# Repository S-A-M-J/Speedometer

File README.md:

# Speedometer
Speedometer based on 7 segment displays and esp32.
Kicad board file is for a Jeep Wrangler YJ.

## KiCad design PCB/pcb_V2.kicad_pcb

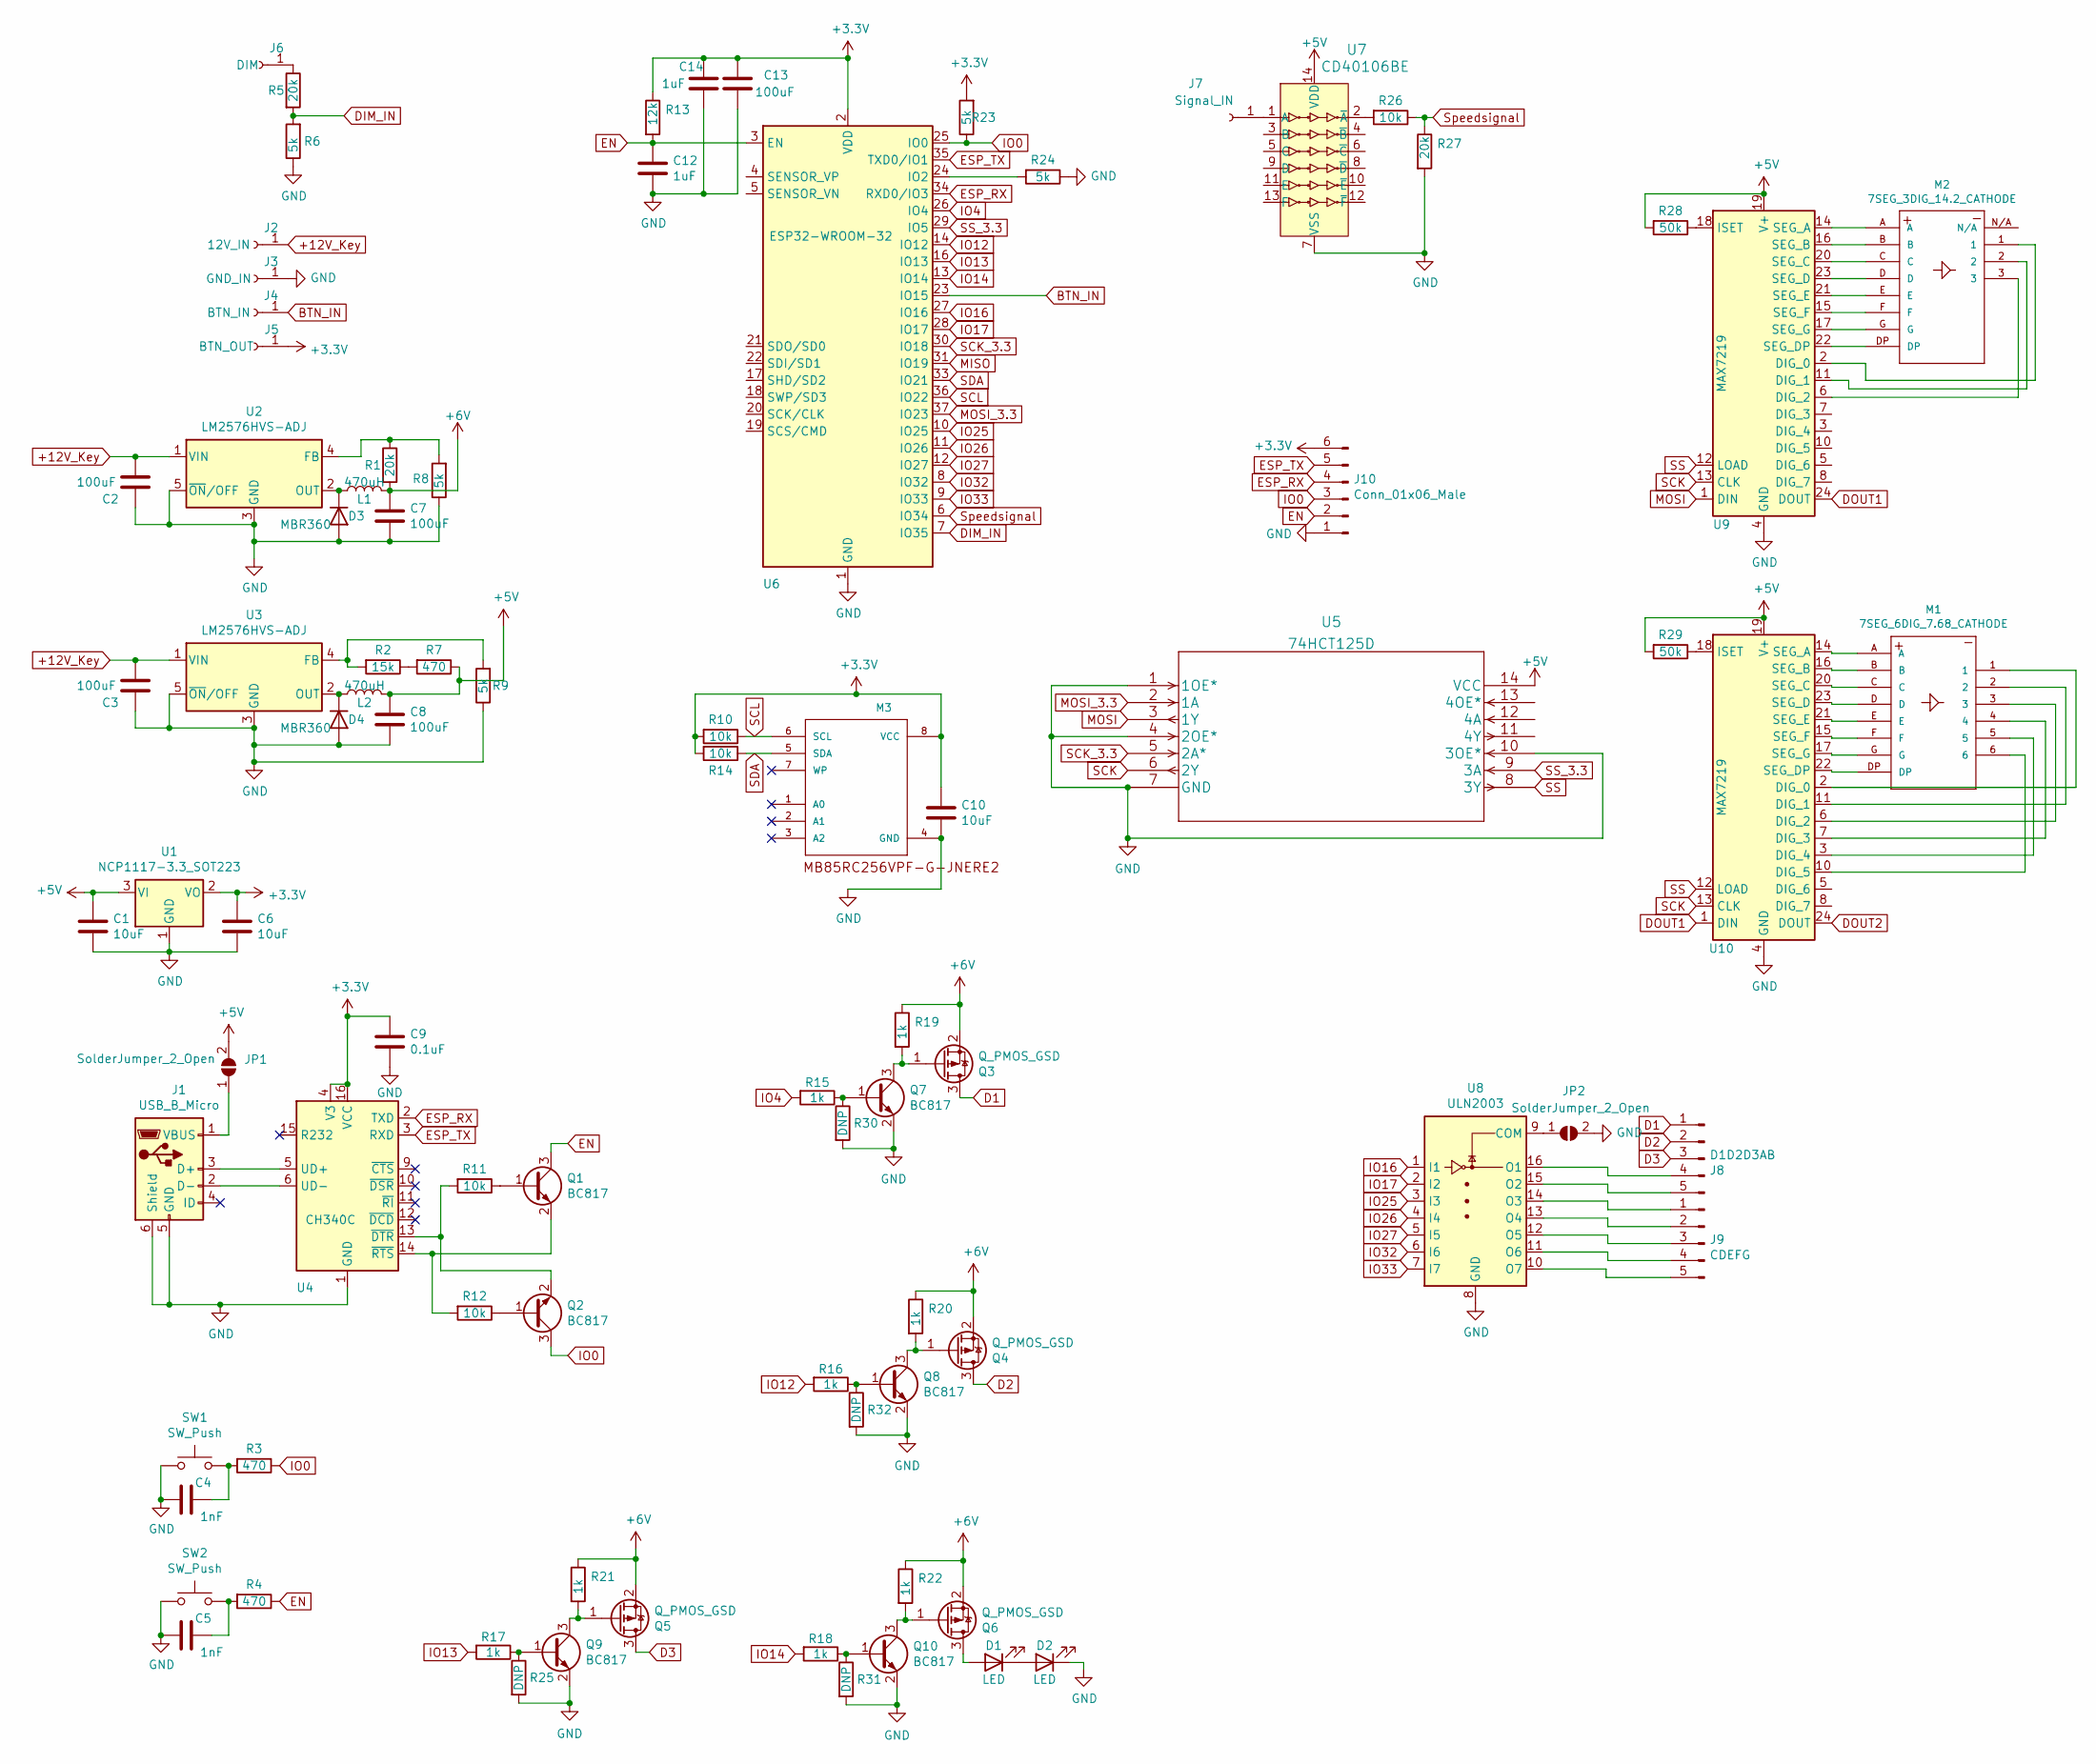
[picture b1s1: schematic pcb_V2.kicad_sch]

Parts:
C1, C6, C10: 10uF; C_0805_2012Metric_Pad1.18x1.45mm_HandSolder
C2, C3, C7, C8, C13: 100uF; CP_Elec_6.3x5.9
C4, C5: 1nF; C_0805_2012Metric_Pad1.18x1.45mm_HandSolder
C9: 0.1uF; C_0805_2012Metric_Pad1.18x1.45mm_HandSolder
C12, C14: 1uF; C_0805_2012Metric_Pad1.18x1.45mm_HandSolder
D1, D2: LED; D_0603_1608Metric_Pad1.05x0.95mm_HandSolder
D3, D4: MBR360; D_SMA_Handsoldering
J1: USB_B_Micro; USB_Micro-B_Molex-105017-0001
J2: 12V_IN; SolderWire-1.5sqmm_1x01_D1.7mm_OD3.9mm
J3: GND_IN; SolderWire-1.5sqmm_1x01_D1.7mm_OD3.9mm
J4: BTN_IN; SolderWire-1.5sqmm_1x01_D1.7mm_OD3.9mm
J5: BTN_OUT; SolderWire-1.5sqmm_1x01_D1.7mm_OD3.9mm
J6: DIM; SolderWire-1.5sqmm_1x01_D1.7mm_OD3.9mm
J7: Signal_IN; SolderWire-1.5sqmm_1x01_D1.7mm_OD3.9mm
J8: D1D2D3AB; PinHeader_1x05_P2.54mm_Vertical
J9: CDEFG; PinHeader_1x05_P2.54mm_Vertical
J10: Conn_01x06_Male; PinHeader_1x06_P2.54mm_Vertical
JP1, JP2: SolderJumper_2_Open; SolderJumper-2_P1.3mm_Open_Pad1.0x1.5mm
L1, L2: 470uH; L_12x12mm_H8mm
M1: 7SEG_6DIG_7.68_CATHODE; 7SEG_6DIG_7.68_Cathode
M2: 7SEG_3DIG_14.2_CATHODE; 7SEG_3DIG_14.2_Cathode
M3: MB85RC256VPF-G-JNERE2; SOP-8_5.28x5.23mm_P1.27mm
Q1, Q2, Q7, Q8, Q9, Q10: BC817; SOT-23
Q3, Q4, Q5, Q6: Q_PMOS_GSD; SOT-23
R1, R5, R27: 20k; R_0805_2012Metric_Pad1.20x1.40mm_HandSolder
R2: 15k; R_0805_2012Metric_Pad1.20x1.40mm_HandSolder
R3, R4, R7: 470; R_0805_2012Metric_Pad1.20x1.40mm_HandSolder
R6, R8, R9, R23, R24: 5k; R_0805_2012Metric_Pad1.20x1.40mm_HandSolder
R10, R11, R12, R14, R26: 10k; R_0805_2012Metric_Pad1.20x1.40mm_HandSolder
R13: 12k; R_0805_2012Metric_Pad1.20x1.40mm_HandSolder
R15, R16, R17, R18, R19, R20, R21, R22: 1k; R_0805_2012Metric_Pad1.20x1.40mm_HandSolder
R25, R30, R31, R32: DNP; R_0805_2012Metric_Pad1.20x1.40mm_HandSolder
R28, R29: 50k; R_0805_2012Metric_Pad1.20x1.40mm_HandSolder
SW1, SW2: SW_Push; SW_Push_1P1T_NO_6x6mm_H9.5mm
U1: NCP1117-3.3_SOT223; SOT-223-3_TabPin2
U2, U3: LM2576HVS-ADJ; TO-263-5_TabPin3
U4: CH340C; SOIC-16_3.9x9.9mm_P1.27mm
U5: 74HCT125D
U6: ESP32-WROOM-32
U7: CD40106BE; DIP-14_W7.62mm_LongPads; MPN CD40106BE; Digi-Key_PN 296-3503-5-ND
U8: ULN2003; SOP-16_4.55x10.3mm_P1.27mm
U9, U10: MAX7219; SOP-24_7.5x15.4mm_P1.27mm

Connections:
+3V3: C6.1, C9.2, C10.1, C13.1, C14.1, J5.1, J10.6, M3.8 (VCC), R10.2, R13.1, R14.2, R23.2, U1.2 (VO), U4.4 (V3), U4.16 (VCC), U6.2 (VDD)
+5V: C1.1, C8.1, JP1.2 (B), L2.2, R7.1, R28.2, R29.2, U1.3 (VI), U5.14 (VCC), U7.14 (VDD), U9.19 (V+), U10.19 (V+)
+6V: C7.1, L1.2, Q3.2 (S), Q4.2 (S), Q5.2 (S), Q6.2 (S), R1.2, R19.1, R20.1, R21.1, R22.1
+12V_Key: C2.1, C3.1, J2.1, U2.1 (VIN), U3.1 (VIN)
BTN_IN: J4.1, U6.23 (IO15)
D1: J8.1, Q3.3 (D)
D2: J8.2, Q4.3 (D)
D3: J8.3, Q5.3 (D)
DIM_IN: R5.2, R6.2, U6.7 (IO35)
DOUT1: U9.24 (DOUT), U10.1 (DIN)
DOUT2: U10.24 (DOUT)
EN: C12.1, J10.2, Q1.3 (C), R4.1, R13.2, U6.3 (EN)
ESP_RX: J10.4, U4.2 (TXD), U6.34 (RXD0/IO3)
ESP_TX: J10.5, U4.3 (RXD), U6.35 (TXD0/IO1)
GND: C1.2, C2.2, C3.2, C4.2, C5.2, C6.2, C7.2, C8.2, C9.1, C10.2, C12.2, C13.2, C14.2, D2.1 (K), D3.2 (A), D4.2 (A), J1.5 (GND), J1.6 (Shield), J3.1, J10.1, JP2.2 (B), M3.4 (GND), Q7.2 (E), Q8.2 (E), Q9.2 (E), Q10.2 (E), R6.1, R8.1, R9.1, R24.1, R25.2, R27.2, R30.2, R31.2, R32.2, SW1.1, SW2.1, U1.1 (GND), U2.3 (GND), U2.5 (~ON/OFF), U3.3 (GND), U3.5 (~ON/OFF), U4.1 (GND), U5.1 (1OE*), U5.4 (2OE*), U5.7 (GND), U5.10 (3OE*), U6.1 (GND), U6.15 (GND), U6.38 (GND), U6.39 (GND), U7.7 (VSS), U8.8 (GND), U9.4 (GND), U9.9 (GND), U10.4 (GND), U10.9 (GND)
IO0: J10.3, Q2.3 (C), R3.1, R23.1, U6.25 (IO0)
IO4: R15.2, U6.26 (IO4)
IO12: R16.2, U6.14 (IO12)
IO13: R17.2, U6.16 (IO13)
IO14: R18.2, U6.13 (IO14)
IO16: U6.27 (IO16), U8.1 (I1)
IO17: U6.28 (IO17), U8.2 (I2)
IO25: U6.10 (IO25), U8.3 (I3)
IO26: U6.11 (IO26), U8.4 (I4)
IO27: U6.12 (IO27), U8.5 (I5)
IO32: U6.8 (IO32), U8.6 (I6)
IO33: U6.9 (IO33), U8.7 (I7)
MISO: U6.31 (IO19)
MOSI: U5.3 (1Y), U9.1 (DIN)
MOSI_3.3: U5.2 (1A), U6.37 (IO23)
unnamed: C4.1, R3.2, SW1.2
unnamed: C5.1, R4.2, SW2.2
unnamed: D1.1 (K), D2.2 (A)
unnamed: D1.2 (A), Q6.3 (D)
unnamed: D3.1 (K), L1.1, U2.2 (OUT)
unnamed: D4.1 (K), L2.1, U3.2 (OUT)
unnamed: J1.1 (VBUS), JP1.1 (A)
unnamed: J1.2 (D-), U4.6 (UD-)
unnamed: J1.3 (D+), U4.5 (UD+)
unnamed: J6.1, R5.1
unnamed: J7.1, U7.1 (A)
unnamed: J8.4, U8.16 (O1)
unnamed: J8.5, U8.15 (O2)
unnamed: J9.1, U8.14 (O3)
unnamed: J9.2, U8.13 (O4)
unnamed: J9.3, U8.12 (O5)
unnamed: J9.4, U8.11 (O6)
unnamed: J9.5, U8.10 (O7)
unnamed: JP2.1 (A), U8.9 (COM)
unnamed: M1.1, U10.2 (DIG_0)
unnamed: M1.2, U10.11 (DIG_1)
unnamed: M1.3, U10.6 (DIG_2)
unnamed: M1.4, U10.7 (DIG_3)
unnamed: M1.5, U10.3 (DIG_4)
unnamed: M1.6, U10.10 (DIG_5)
unnamed: M1.A, U10.14 (SEG_A)
unnamed: M1.B, U10.16 (SEG_B)
unnamed: M1.C, U10.20 (SEG_C)
unnamed: M1.D, U10.23 (SEG_D)
unnamed: M1.DP, U10.22 (SEG_DP)
unnamed: M1.E, U10.21 (SEG_E)
unnamed: M1.F, U10.15 (SEG_F)
unnamed: M1.G, U10.17 (SEG_G)
unnamed: M2.1, U9.2 (DIG_0)
unnamed: M2.2, U9.11 (DIG_1)
unnamed: M2.3, U9.6 (DIG_2)
unnamed: M2.A, U9.14 (SEG_A)
unnamed: M2.B, U9.16 (SEG_B)
unnamed: M2.C, U9.20 (SEG_C)
unnamed: M2.D, U9.23 (SEG_D)
unnamed: M2.DP, U9.22 (SEG_DP)
unnamed: M2.E, U9.21 (SEG_E)
unnamed: M2.F, U9.15 (SEG_F)
unnamed: M2.G, U9.17 (SEG_G)
unnamed: Q1.1 (B), R11.1
unnamed: Q1.2 (E), R12.2, U4.14 (~RTS)
unnamed: Q2.1 (B), R12.1
unnamed: Q2.2 (E), R11.2, U4.13 (~DTR)
unnamed: Q3.1 (G), Q7.3 (C), R19.2
unnamed: Q4.1 (G), Q8.3 (C), R20.2
unnamed: Q5.1 (G), Q9.3 (C), R21.2
unnamed: Q7.1 (B), R15.1, R30.1
unnamed: Q8.1 (B), R16.1, R32.1
unnamed: Q9.1 (B), R17.1, R25.1
unnamed: Q10.1 (B), R18.1, R31.1
unnamed: Q6.1 (G), Q10.3 (C), R22.2
unnamed: R1.1, R8.2, U2.4 (FB)
unnamed: R2.1, R7.2
unnamed: R2.2, R9.2, U3.4 (FB)
unnamed: R24.2, U6.24 (IO2)
unnamed: R26.2, U7.2 (~A)
unnamed: R28.1, U9.18 (ISET)
unnamed: R29.1, U10.18 (ISET)
SCK: U5.6 (2Y), U9.13 (CLK), U10.13 (CLK)
SCK_3.3: U5.5 (2A*), U6.30 (IO18)
SCL: M3.6 (SCL), R10.1, U6.36 (IO22)
SDA: M3.5 (SDA), R14.1, U6.33 (IO21)
SS: U5.8 (3Y), U9.12 (LOAD), U10.12 (LOAD)
SS_3.3: U5.9 (3A), U6.29 (IO5)
Speedsignal: R26.1, R27.1, U6.6 (IO34)

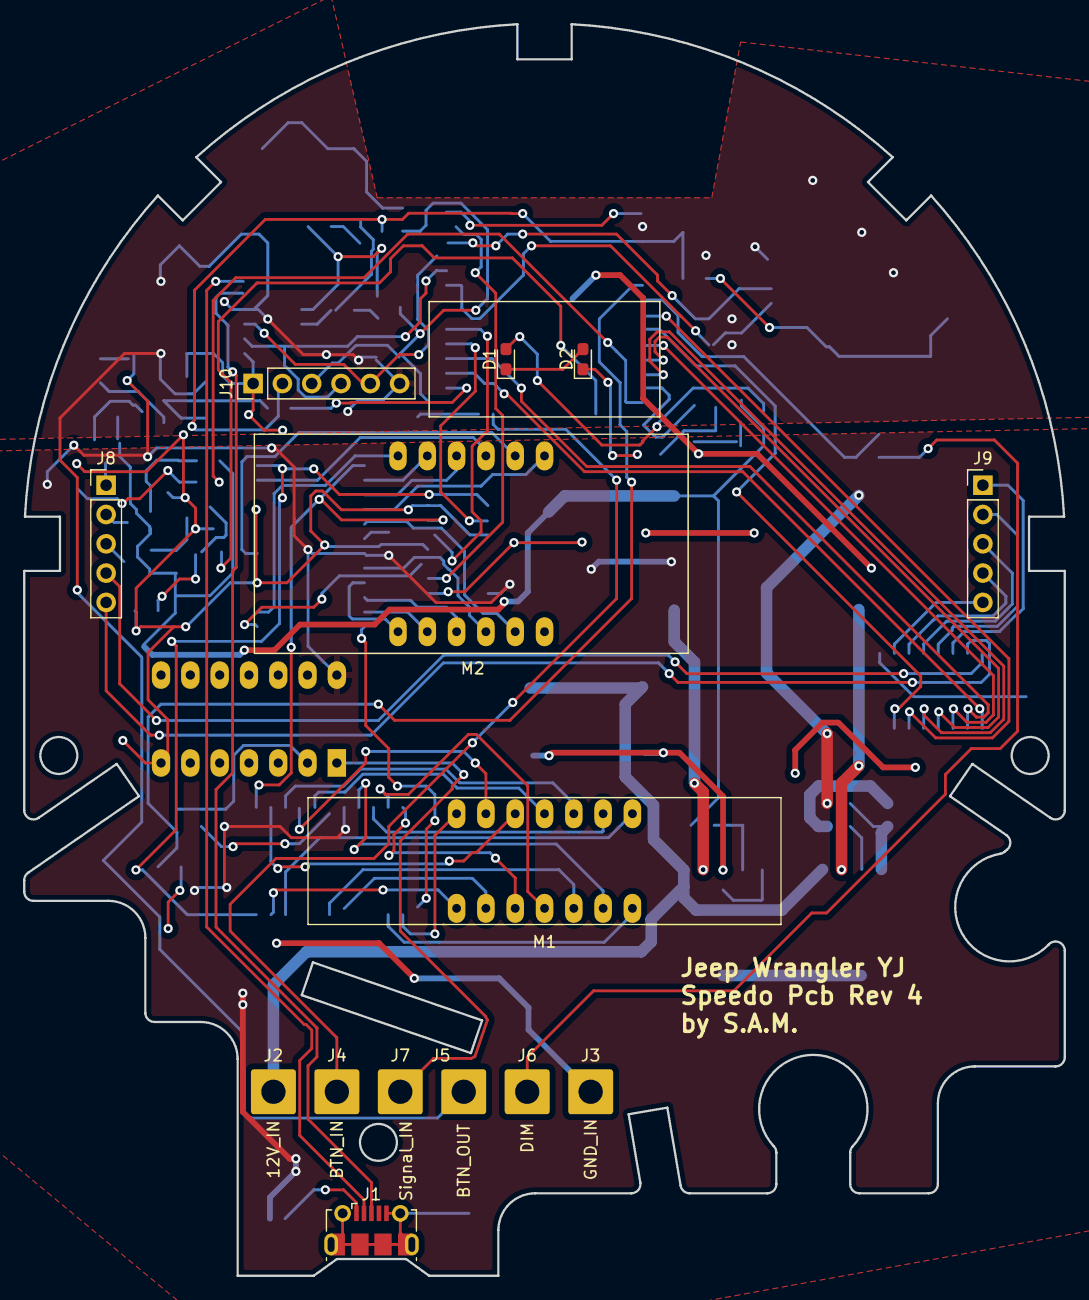
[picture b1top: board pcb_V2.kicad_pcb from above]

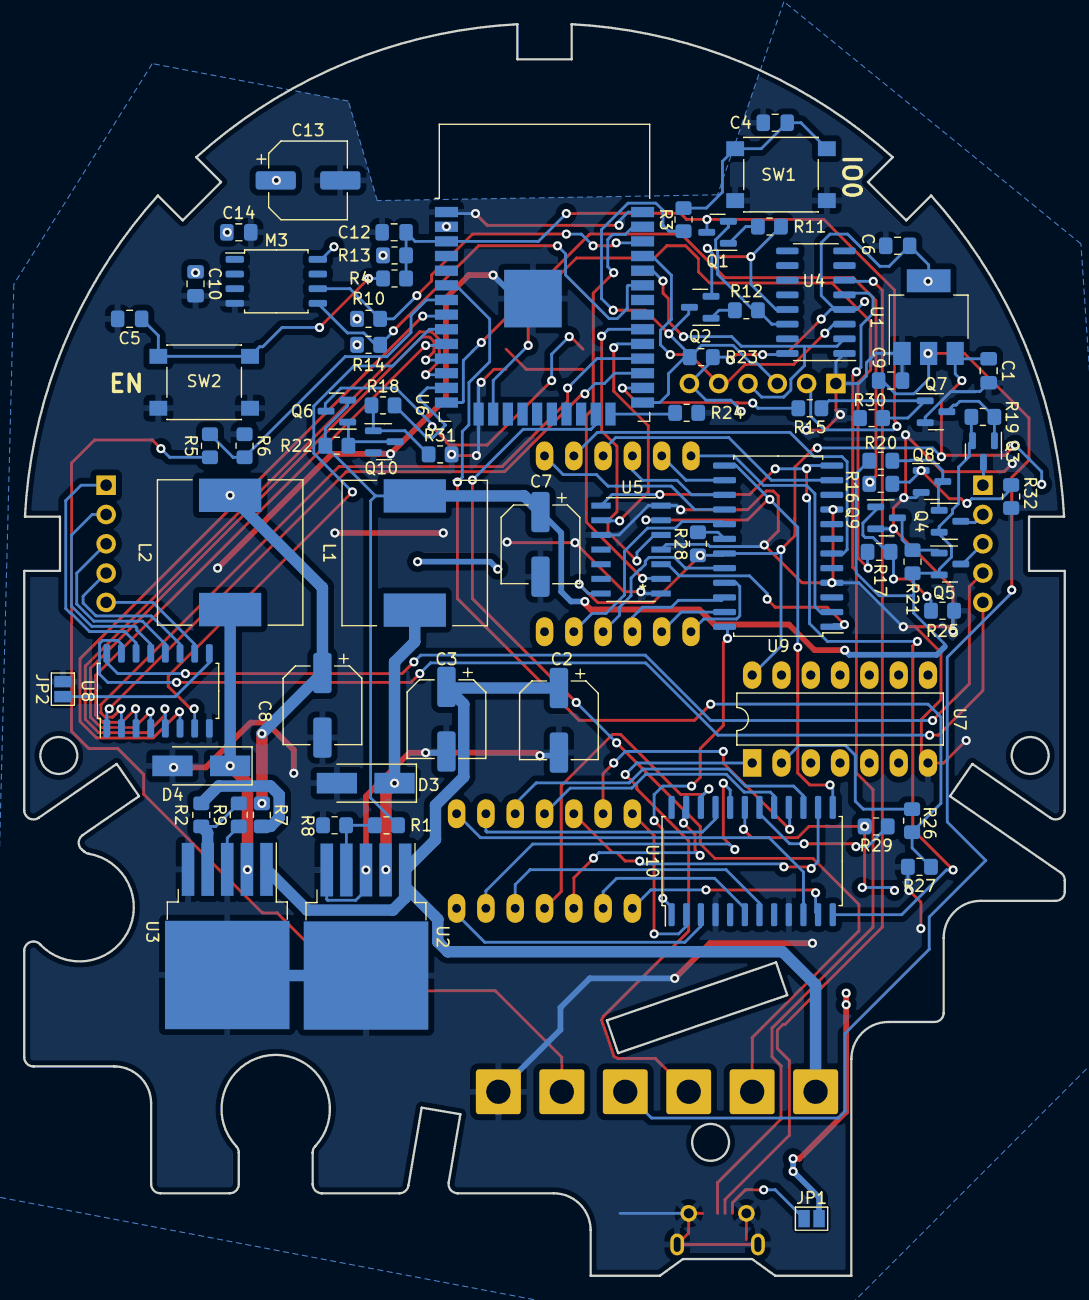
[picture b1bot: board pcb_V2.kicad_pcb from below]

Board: 2 copper layers, 90.2 x 108.5 mm, 88 parts (74 on the bottom side), 98 nets.

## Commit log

2022-03-12 Add files via upload
    arduino ide based sketch for esp32
2023-05-24 updated firmware completetly
2023-05-24 updated Firmware
2023-05-24 added webpage configurator
2023-05-24 deleted unnecessary images
2023-05-24 fixed str.match error
2023-05-25 fixed isConnected error

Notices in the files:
parts and their libraries:
Copyright 2021 Accelerated Designs. All rights reserved.
